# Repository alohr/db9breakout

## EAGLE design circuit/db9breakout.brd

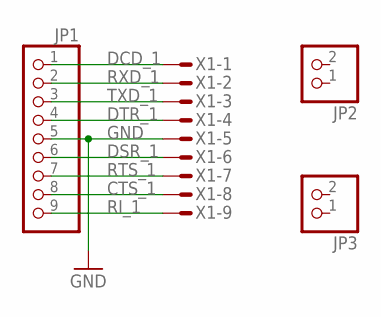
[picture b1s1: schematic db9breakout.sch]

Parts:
JP1: PINHD-1X9; 1X09
JP2, JP3: PINHD-1X2; 1X02
X1: M09HPS; M09HP

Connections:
CTS_1: JP1.8, X1.8
DCD_1: JP1.1, X1.1
DSR_1: JP1.6, X1.6
DTR_1: JP1.4, X1.4
GND: JP1.5, X1.5
RI_1: JP1.9, X1.9
RTS_1: JP1.7, X1.7
RXD_1: JP1.2, X1.2
TXD_1: JP1.3, X1.3

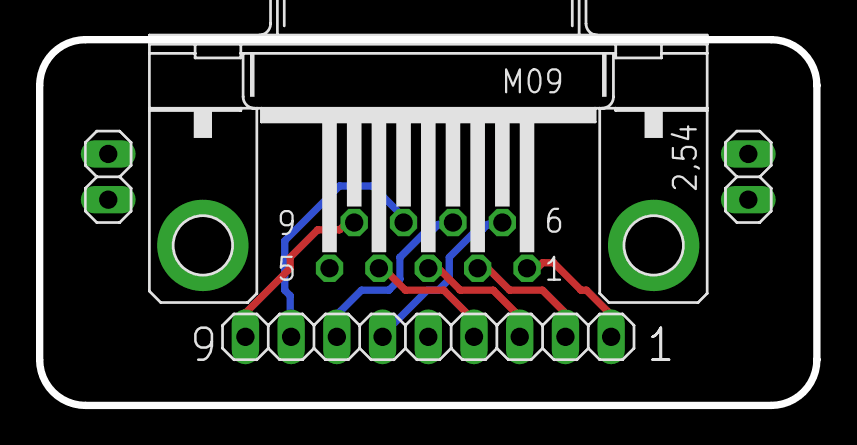
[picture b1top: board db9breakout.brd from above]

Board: 2 copper layers, 43.2 x 20.3 mm, 4 parts (0 on the bottom side), 9 nets.
